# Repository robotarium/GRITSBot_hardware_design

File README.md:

- [Overview](#overview)
- [Getting Started](#getting-started)
- [Hardware Specifications](#hardware-specifications)
- [Hardware Assembly](#hardware-assembly)

# Overview
This repository contains the GRITSBot's circuit board designs, bill of materials, hardware specifications, and 3D design files. This README file is meant to provide more detailed hardware specifications and a brief tutorial outlining how to get started with the hardware. Specifically, it explains how to program both the motor and the main board.

# Getting Started
The newest version of the GRITSBot features two microcontrollers - an Atmega168/328 (8MHz, 16/32 KB flash, 2 KB RAM) on the motor board and the ESP8266 (80/160 MHz, ~80kB DRAM (Data RAM), ~35kB IRAM (Instruction RAM)) on the main board. Both boards can be programmed through the Arduino IDE but require different toolchains (avr-gcc and Xtensa). Both boards have broken out pins to connect the programmer to. The motor board relies on SPI communication for programming, while the main board's ESP8266 chip has a built-in serial bootloader. Therefore the main board requires only a USB-to-TTL converter to program instead of a programmer for the motor board. Note that for programming, the robot has to be disassembled, i.e. the two boards have to be taken apart (the battery does not have to be disconnected, but it's advisable that the robot's power switch is in the OFF position).

## Motor board programming
The GRITSBot's motor board firmware is available [here](https://github.com/robotarium/GRITSBot_firmware). Before programming the motor board, download all required libraries from that link and copy them to the Arduino IDE's 'libraries' folder.

1. Connect the 6-pin ISP single row programming header (shown in the picture) to the female SPI header pins on the motor board (note that for size reasons, the programming connector on the motor board is a two-row 0.127 inch pitch connector and may require an adapter.)
2. Plug the programmer into the USB port on your host machine (ideally running Linux).
3. Programming the Atmega168/328 chip can be done in a variety of ways 
  * Use a tool called arduino-cmake, a CMake-based toolchain customized for the use of avrdude. The initial setup can be tricky but the tool itself is convenient.
  * Add a board definition to the Arduino IDE's boards.txt file that allows direct programming of the motor board through a programming device in the Arduino IDE.
  * If you have compiled your code already and have a .hex file ready to go, you can use avrdude directly as shown below.

An example of uploading a compiled hex file is shown in the line below, which uploads the "blink.hex" file to the flash memory of an Atmega328 chip through the USB port with the help of an STK500v2 programmer. In the call to _avrdude_ you can see the _-C_ parameter to include its configuration file _avrdude.conf_.
```
avrdude -C avrdude.conf -v -v -v -patmega328 -cstk500v2 -Pusb -Uflash:w:./blink.hex:i -Ulock:w:0x0F:m

```

## Main board programming 
Programming the main board is simpler, since it can be done via a serial adapter. However, attention has to be paid to the operating voltage of the main board, which is 3.3V. The ESP8266 chip is NOT 5V-tolerant and both the supply voltage as well as the serial data signals have to be 3.3V. The following steps assume that your Arduino IDE is set up according to [Sparkfun's tutorial](https://learn.sparkfun.com/tutorials/esp8266-thing-hookup-guide/installing-the-esp8266-arduino-addon). It also assumes that you have downloaded all the GRITSBot's firmware libraries into your Arduino/libraries folder. Then the following steps will program the main board. Note that the GRITSBot's main board firmware is available [here](https://github.com/robotarium/GRITSBot_firmware).

1. Set the "Bootmode" switch on the main board to "Flash" (this ensures that the GPIO0 of the ESP8266 is pulled to logic LOW).
2. Press the push botton on the board to reset the board into programming mode in case the board was powered on before.
3. Select *Generic ESP8266 Module* in the board list of the Arduino IDE (Upload speed can be as high as 921000 Baud, depending on your FTDI adapter).
4. Connect the FTDI serial adapter to the main board and plug the other end into a USB port. Make sure the adapter operates at 3.3V (the broken out pins on the main board contain TX, RX, VCC, and GND).
5. Upload code to the board through the Arduino IDE.

# Hardware Specifications
The robot consists of two individual boards that are stacked through a combination of male and female header pins. 

The main board is the central processing board and responsible for the high-level control of the robot, communication, and power supply. As such, it contains the main microcontroller and a WiFi transceiver. The following list summarizes the main components of the main board.

1. The ESP8266 microcontroller that also hosts the WiFi hardware and runs the WiFi stack in software. The ESP8266 chip contains an SPI-controlled EEPROM chip that enables the chip to be wirelessly reprogrammed. The newest version of the GRITSBot contains the ESP8266 12-E with 4 MB (32 MBit) of flash memory, which allows firmware upgrades over-the-air ([see Adafruit](https://www.adafruit.com/products/2491)).
2. MCP73831 LiPo battery charging chip
3. AP2112K-3.3V 3.3V voltage regulator (capable of providing 600 mA of current, which is necessary since the ESP8266 can have peak current consumptions of 300 mA)
4. MCP1640 step-up converter for powering the motors on the motor board (capable of providing 150 mA)
5. INA219 I2C-enabled current and voltage sensor 
6. ATECC108 encryption and authentication chip

The following two images show the top and the bottom layer of the main board PCV

The motor board contains all components related to locomotion including a microcontroller to control the stepper motors. An additional EEPROM chip allows storing calibration parameters and equips each motor board with a unique ID. Additionally, the motor board contains downward-facing infrared sensors for line-following applications as well as introspective sensors to measure the state of the motor board (e.g. currents and temperatures).

1. One Atmega168/328 microcontroller (the motor board firmware requires over 9 KB which excludes the Atmega88 chip)
2. Two LB1836M motor drivers
3. Two miniature stepper motors
4. One 24AA025UIDT-I/OT 2KBIT I2C EEPROM chip providing a unique ID to each motor board.
5. Two QRE1113 downward-facing infrared line sensors 
6. Two STLM20 temperature sensors measuring motor temperatures
7. Two ZXCT1009 current sensors measuring motor currents
6. Reverse polarity circuitry protecting charger input pins
7. Two LEDs for visual output and debugging

The following two images show the top and the bottom layer of the main board PCV

# Hardware Assembly
Assembly of the GRITSBot is fairly simple in the sense that few components have to be added once all the circuit boards have been populated with SMD components (services such as Seeedstudio or Circuithub can manufacture and populate the boards for a reasonable price). Manufacturers can also populate the throughhole components (i.e. the male and female header pins) but so far we have done that manually. The main and motor boards have matching male/female headers that can only be stacked in one way. The __assembly sequence__ contains the following steps. 

## Main board assembly
1. Solder a female Losi Micro Walkera 2-Pin Connector plug to the main board's battery pins (i.e. VBAT and neighboring GND pin)
2. Solder a 4-pin male programming header pin to the top of the main board (i.e. the pins TX, RX, Vcc, GND). Note that the top side of the board is the one with the ESP8266 12-E part.
3. Solder four 2-pin male header pins to all four corners on the bottom of the main board. In the schematic and board files, these pins are labeled JP\_RST, JP\_I2C, JP\_GND, and JP\_VCHRG\_IN.
4. Solder a 3-pin female header pin to the power pins in the center of the bottom of the board (labeled "MOTOR", containing the pins Vcc, Vdd, and GND).

## Motor board assembly
The motor board assembly contains a few more steps since the motors have to be soldered on besides the male and female header pins. In addition, the Qi charging coil and receiver circuitry have to be attached to the board. 

### Prepare and mount the motors and wheels
1. Tap the wheels with an M1.7 thread plug.
2. Screw one wheel onto each motor.
3. Solder both motors onto the motor board (a video showing this procedure will follow soon)

### Solder on the connectors
1. Solder four 2-pin female header pins to all four corners on the top of the motor board. In the schematic and board files, these pins are labeled JP\_RST, JP\_I2C, JP\_GND, and JP\_VCHRG.
2. Solder a 3-pin male header pin to the power pins in the center of the top of the motor board (containing the pins Vcc, Vdd, and GND).

### Prepare the Qi receiver parts
1. Disassemble the Qi receiver pad (see bill of materials specifying which receiver pad to purchase).
2. Desolder the USB connector and the coil from the receiver assembly.

### Attach the Qi receiver parts
1. Glue or tape the Qi receiver coil to the 3D part [Charging Coil Base](https://github.com/robotarium/GRITSBot_hardware_design/blob/master/3d_model/Charging_frame_base.stp).
2. Tape the Qi receiver circuitry to the top of the motor board.
3. Solder a wire to each output pin of the receiver circuitry (those pins should be labeled '+' and '-' or '5V' and 'Gnd').
4. Solder the other end of these wires to the following motor board pins: JP\_CHRG\_L and JP\_CHRG\_R
5. Cut the receiver coil wires to the right length and solder them to the input pins of the receiver circuitry. Those pins may not be labeled on the receiver circuitry, but attach them to the same pins that you desoldered them before.

## Robot assembly
2. Sandwich the battery between the motor and the main board and wrap the battery cable around the robot.
3. Stack the motor and the main board keeping the battery in place.
5. Connect battery to the main board.

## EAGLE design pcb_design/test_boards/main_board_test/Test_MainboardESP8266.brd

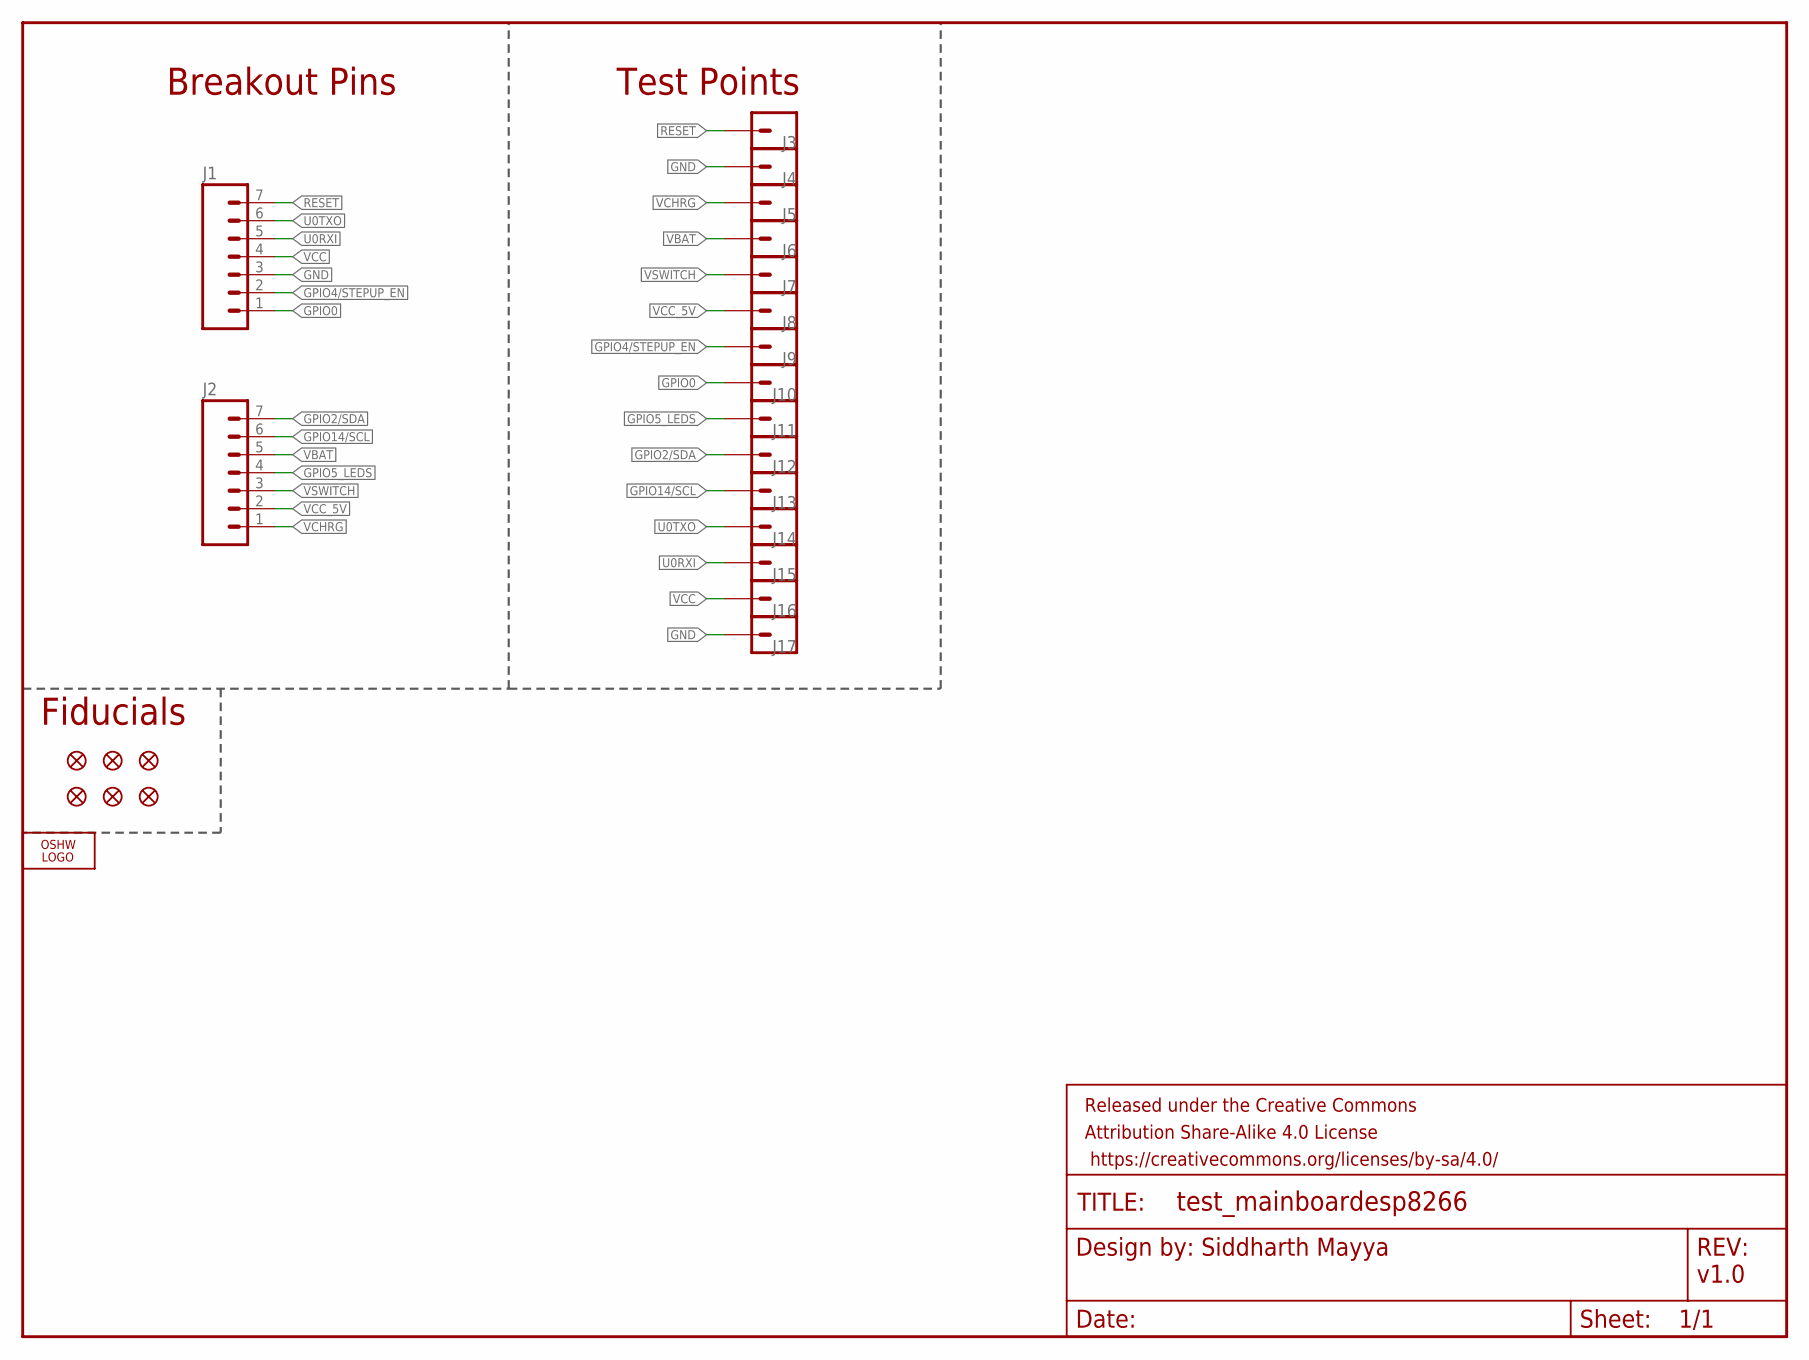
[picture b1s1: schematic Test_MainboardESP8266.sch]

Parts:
FD1, FD2, FD3, FD4, FD5, FD6: FIDUCIAL1X2; FIDUCIAL-1X2
FRAME1: FRAME-LETTER; CREATIVE_COMMONS
J1, J2: M07; 1X07
J3, J4, J5, J6, J7, J8, J9, J10, J11, J12, J13, J14, J15, J16, J17: M01PTH; 1X01
LOGO1: OSHW_LOGO_FILLX0100-NT; OSHW_FILLX100_NOTEXT

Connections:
GND: J1.3, J4.1, J17.1
GPIO0: J1.1, J10.1
GPIO2/SDA: J2.7, J12.1
GPIO4/STEPUP_EN: J1.2, J9.1
GPIO5_LEDS: J2.4, J11.1
GPIO14/SCL: J2.6, J13.1
RESET: J1.7, J3.1
U0RXI: J1.5, J15.1
U0TXO: J1.6, J14.1
VBAT: J2.5, J6.1
VCC: J1.4, J16.1
VCC_5V: J2.2, J8.1
VCHRG: J2.1, J5.1
VSWITCH: J2.3, J7.1

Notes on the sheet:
v1.0
Test Points
Breakout Pins
Fiducials

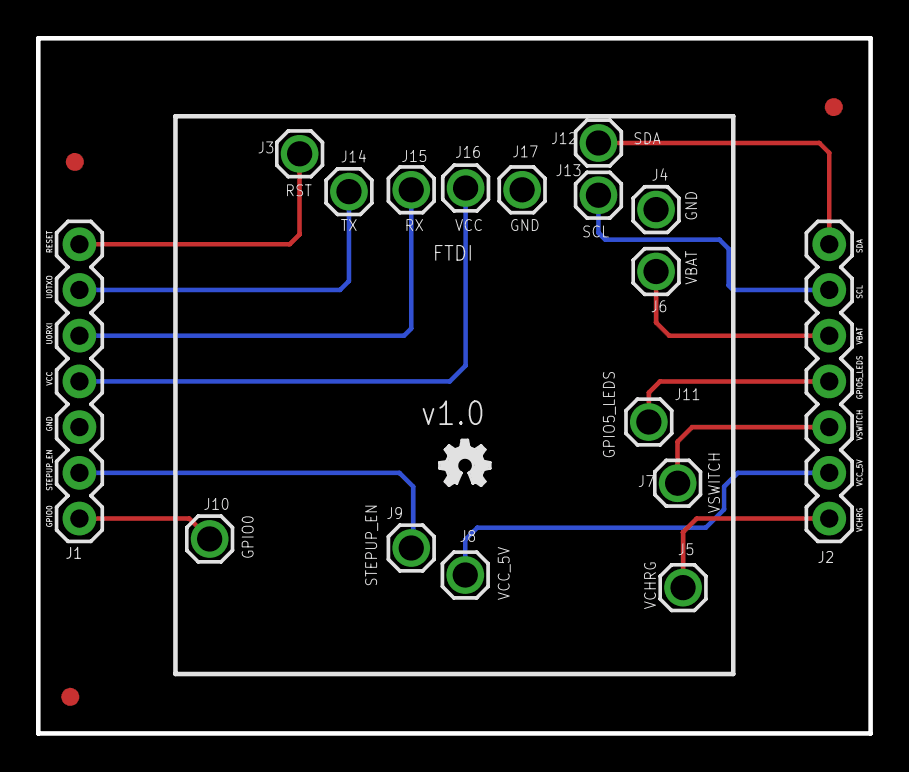
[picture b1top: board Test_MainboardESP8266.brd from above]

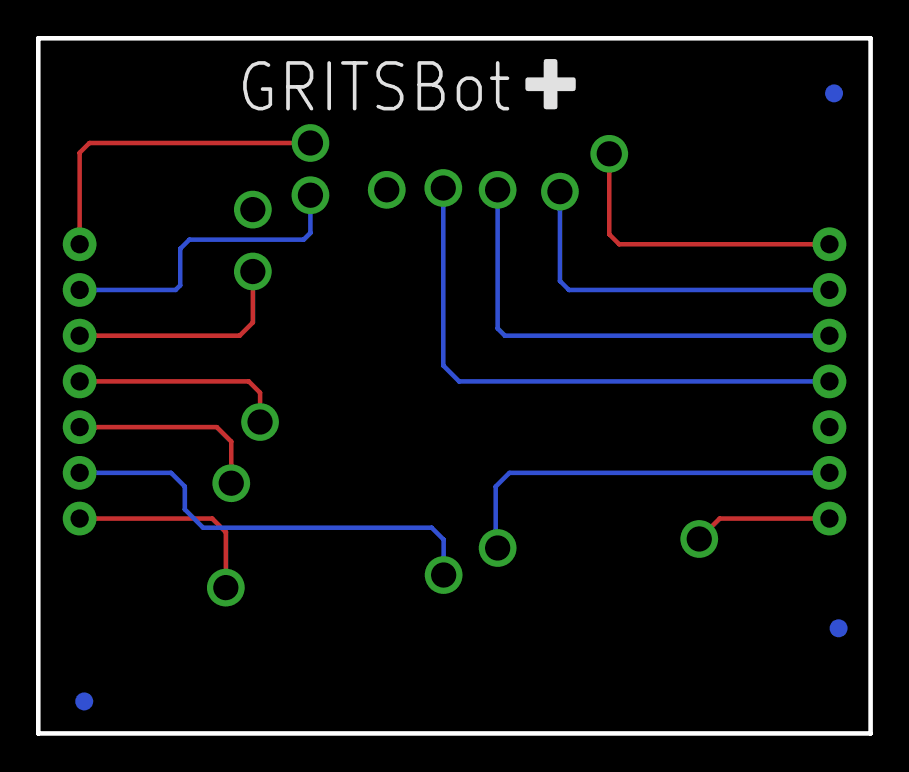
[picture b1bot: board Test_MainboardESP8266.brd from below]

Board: 2 copper layers, 46.2 x 38.6 mm, 25 parts (3 on the bottom side), 14 nets.

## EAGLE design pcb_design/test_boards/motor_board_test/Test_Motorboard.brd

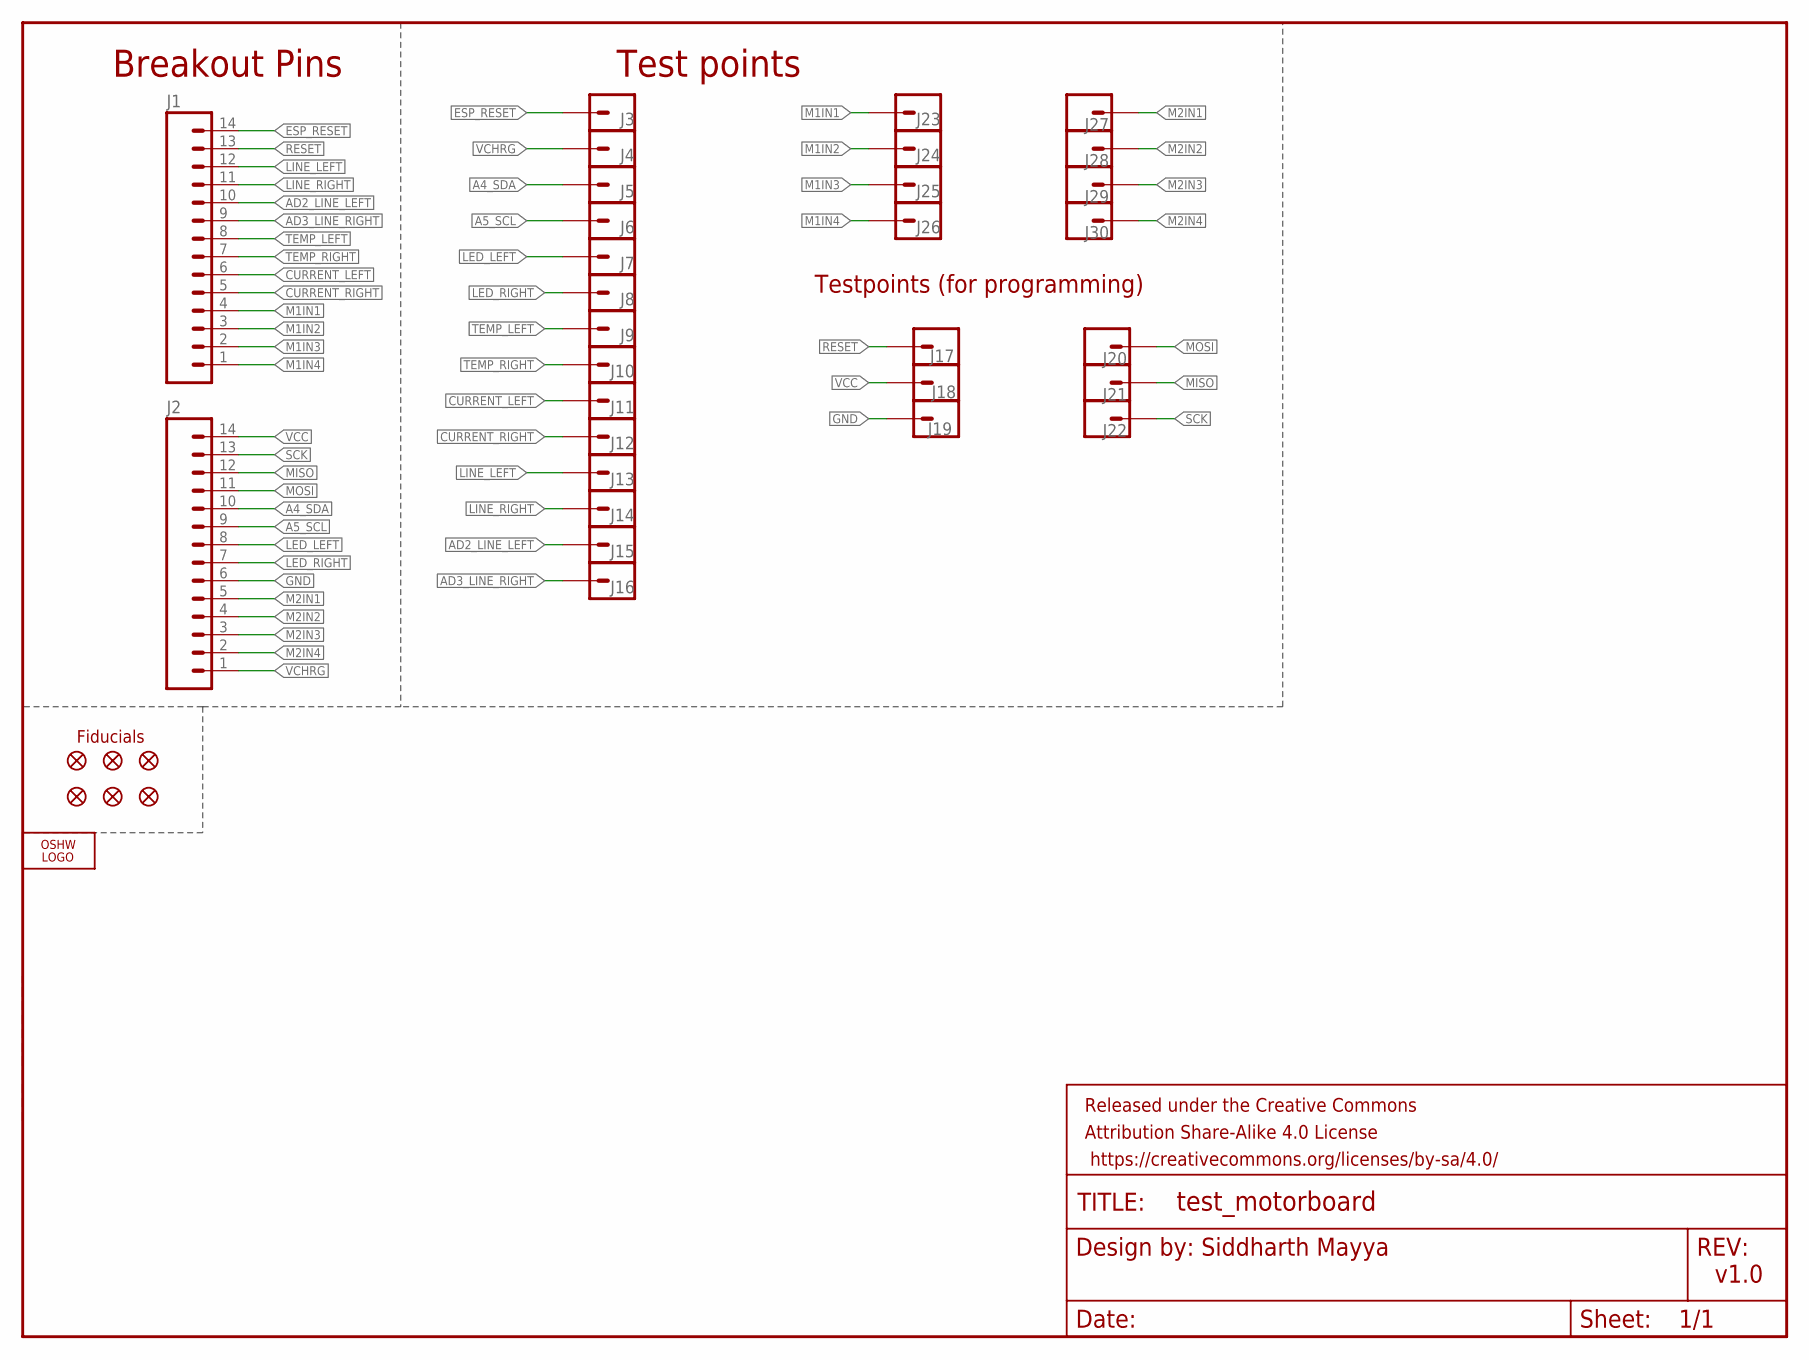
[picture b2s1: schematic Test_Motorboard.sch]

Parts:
FD1, FD2, FD3, FD4, FD5, FD6: FIDUCIAL1X2; FIDUCIAL-1X2
FRAME1: FRAME-LETTER; CREATIVE_COMMONS
J1, J2: M14; 1X14
J3, J4, J5, J6, J7, J8, J9, J10, J11, J12, J13, J14, J15, J16, J17, J18, J19, J20, J21, J22, J23, J24, J25, J26, J27, J28, J29, J30: M01PTH; 1X01
LOGO1: OSHW_LOGO_FILLX0100-NT; OSHW_FILLX100_NOTEXT

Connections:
A4_SDA: J2.10, J5.1
A5_SCL: J2.9, J6.1
AD2_LINE_LEFT: J1.10, J15.1
AD3_LINE_RIGHT: J1.9, J16.1
CURRENT_LEFT: J1.6, J11.1
CURRENT_RIGHT: J1.5, J12.1
ESP_RESET: J1.14, J3.1
GND: J2.6, J19.1
LED_LEFT: J2.8, J7.1
LED_RIGHT: J2.7, J8.1
LINE_LEFT: J1.12, J13.1
LINE_RIGHT: J1.11, J14.1
M1IN1: J1.4, J23.1
M1IN2: J1.3, J24.1
M1IN3: J1.2, J25.1
M1IN4: J1.1, J26.1
M2IN1: J2.5, J27.1
M2IN2: J2.4, J28.1
M2IN3: J2.3, J29.1
M2IN4: J2.2, J30.1
MISO: J2.12, J21.1
MOSI: J2.11, J20.1
RESET: J1.13, J17.1
SCK: J2.13, J22.1
TEMP_LEFT: J1.8, J9.1
TEMP_RIGHT: J1.7, J10.1
VCC: J2.14, J18.1
VCHRG: J2.1, J4.1

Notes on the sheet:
Breakout Pins
Testpoints (for programming)
Test points
Fiducials
v1.0

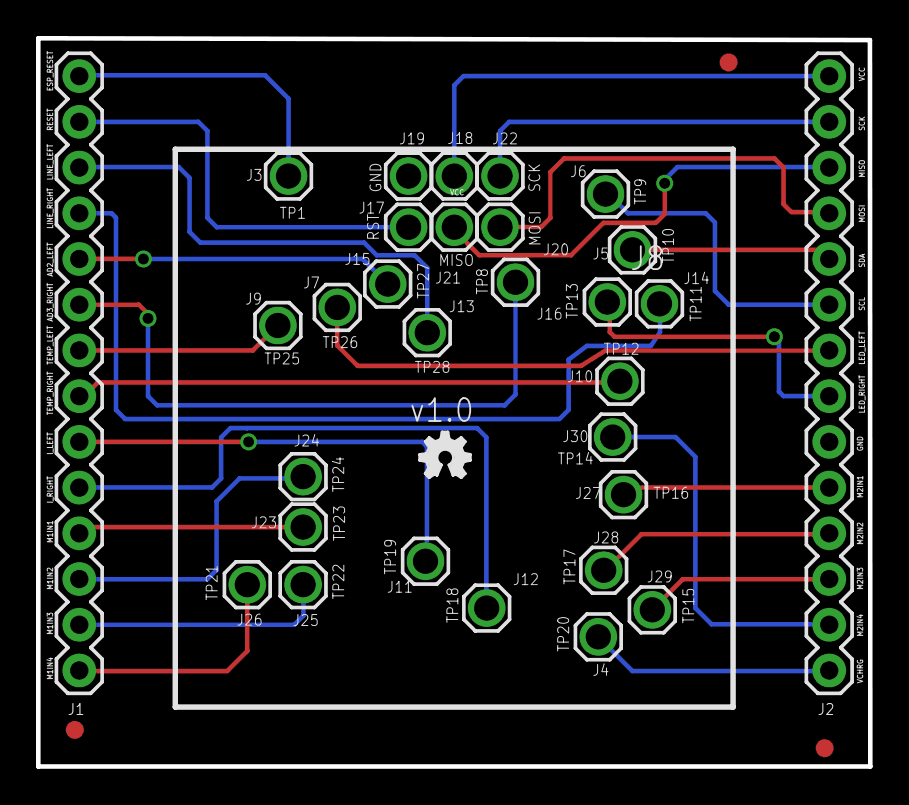
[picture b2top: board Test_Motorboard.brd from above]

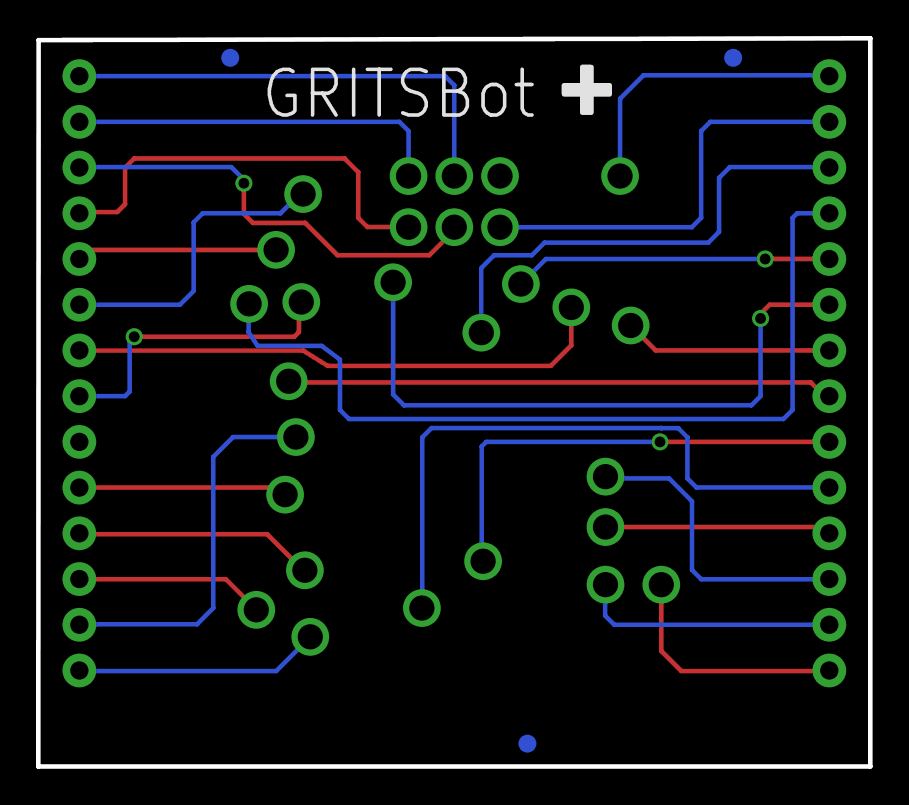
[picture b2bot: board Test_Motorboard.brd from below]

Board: 2 copper layers, 46.2 x 40.5 mm, 39 parts (3 on the bottom side), 28 nets.

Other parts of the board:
FRAME3: FRAME-LETTER; CREATIVE_COMMONS

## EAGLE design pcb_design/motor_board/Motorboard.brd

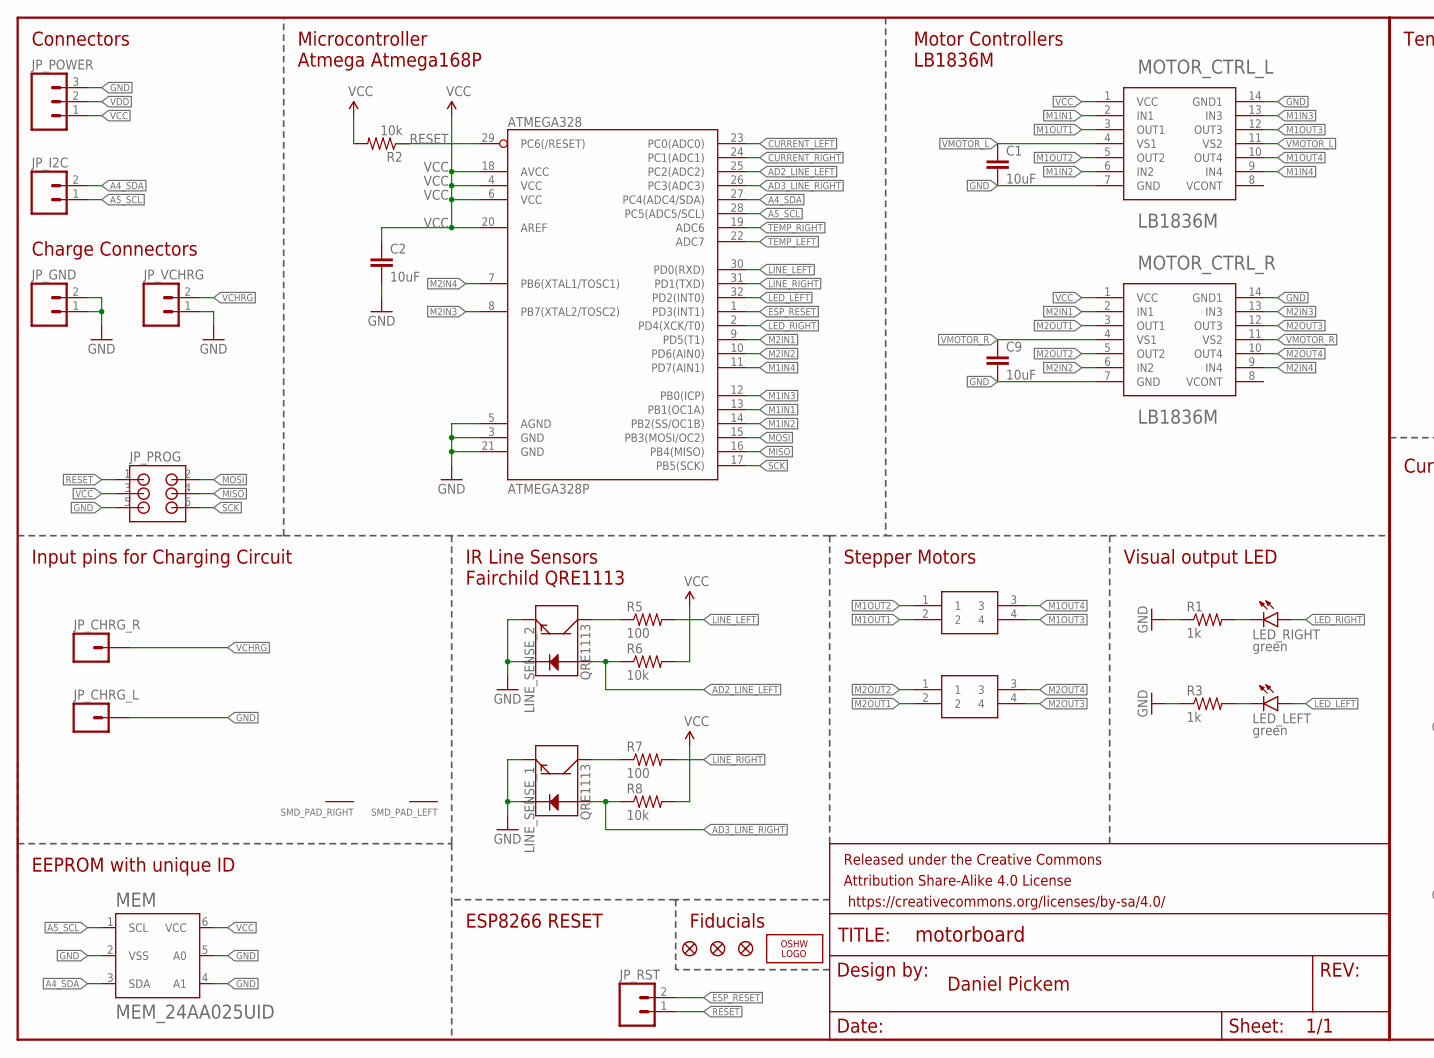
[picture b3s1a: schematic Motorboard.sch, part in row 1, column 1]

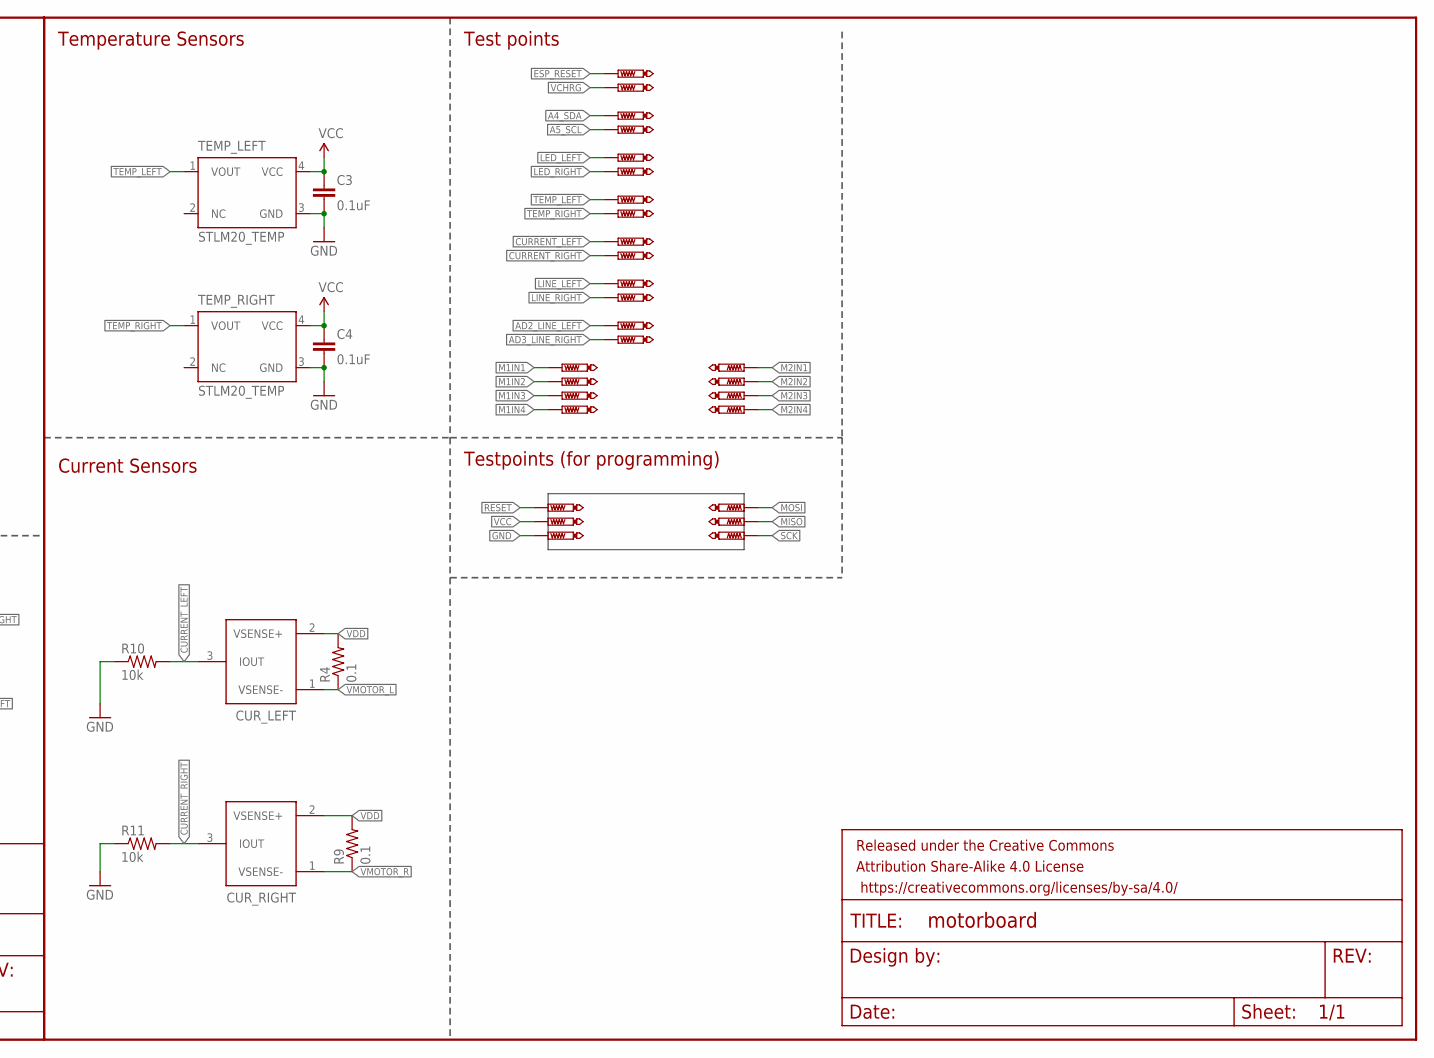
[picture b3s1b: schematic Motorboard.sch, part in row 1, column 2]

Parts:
ATMEGA328P: ATMEGA328; TQFP32-08
C1, C2, C9: 10uF; 0805
C3, C4: 0.1uF; 0603-CAP
CUR_LEFT: ZXCT1009_CURRENT; SOT23-3
CUR_RIGHT: ZXCT1009_CURRENT; SOT23-3
FRAME1, FRAME2: FRAME-LETTER; CREATIVE_COMMONS
JP3, JP4, JP5: FIDUCIAL1X2.5; FIDUCIAL-1X2.5
JP_CHRG_L: M01NOSILK-KIT; 1X01NS-KIT
JP_CHRG_R: M01NOSILK-KIT; 1X01NS-KIT
JP_GND: M021X02_NO_SILK; 1X02_NO_SILK
JP_I2C: M02PTH; 1X02
JP_POWER: supply; 1X03
JP_PROG: 3X2_SMD_HEADER
JP_RST: M021X02_NO_SILK; 1X02_NO_SILK
JP_VCHRG: M021X02_NO_SILK; 1X02_NO_SILK
LED_LEFT: green; LED-0603
LED_RIGHT: green; LED-0603
LINE_SENSE_1, LINE_SENSE_2: QRE1113
LOGO1: OSHW_LOGO_FILLX0100-NT; OSHW_FILLX100_NOTEXT
M1, M2: STEPPER_MOTOR_SMD
MEM: MEM_24AA025UID; SOT23-6-MCP1640
MOTOR_CTRL_L: LB1836M; LSOP-14
MOTOR_CTRL_R: LB1836M; LSOP-14
R1, R3: 1k; 0603
R2, R6, R8, R10, R11: 10k; 0603
R4, R9: 0.1; 1206
R5, R7: 100; 0603
SMD_PAD_LEFT: PIN_SMD2.5X1.0; PIN_SMD_2.5X1.0
SMD_PAD_RIGHT: PIN_SMD2.5X1.0; PIN_SMD_2.5X1.0
TEMP_LEFT: STLM20_TEMP; UDFN4
TEMP_RIGHT: STLM20_TEMP; UDFN4
TP1, TP2, TP3, TP4, TP5, TP6, TP7, TP8, TP9, TP10, TP11, TP12, TP13, TP14, TP15, TP16, TP17, TP18, TP19, TP20, TP21, TP22, TP23, TP24, TP25, TP26, TP27, TP28: PTR1B1,27; B1,27

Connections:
A4_SDA: ATMEGA328P.27 (PC4(ADC4/SDA)), JP_I2C.2, MEM.3 (SDA), TP10.TP
A5_SCL: ATMEGA328P.28 (PC5(ADC5/SCL)), JP_I2C.1, MEM.1 (SCL), TP9.TP
AD2_LINE_LEFT: ATMEGA328P.25 (PC2(ADC2)), LINE_SENSE_2.1 (A), R6.1, TP27.TP
AD3_LINE_RIGHT: ATMEGA328P.26 (PC3(ADC3)), LINE_SENSE_1.1 (A), R8.1, TP8.TP
CURRENT_LEFT: ATMEGA328P.23 (PC0(ADC0)), CUR_LEFT.3 (IOUT), R10.2, TP19.TP
CURRENT_RIGHT: ATMEGA328P.24 (PC1(ADC1)), CUR_RIGHT.3 (IOUT), R11.2, TP18.TP
ESP_RESET: ATMEGA328P.1 (PD3(INT1)), JP_RST.2, TP1.TP
GND: ATMEGA328P.3 (GND), ATMEGA328P.5 (AGND), ATMEGA328P.21 (GND), C1.2, C2.2, C3.2, C4.1, C9.2, JP_CHRG_L.1, JP_GND.1, JP_GND.2, JP_POWER.3, JP_PROG.5, JP_VCHRG.1, LINE_SENSE_1.2 (K), LINE_SENSE_1.4 (E), LINE_SENSE_2.2 (K), LINE_SENSE_2.4 (E), MEM.2 (VSS), MEM.4 (A1), MEM.5 (A0), MOTOR_CTRL_L.7 (GND), MOTOR_CTRL_L.14 (GND1), MOTOR_CTRL_R.7 (GND), MOTOR_CTRL_R.14 (GND1), R1.1, R3.1, R10.1, R11.1, TEMP_LEFT.3 (GND), TEMP_RIGHT.3 (GND), TP2.TP
LED_LEFT: ATMEGA328P.32 (PD2(INT0)), LED_LEFT.A, TP26.TP
LED_RIGHT: ATMEGA328P.2 (PD4(XCK/T0)), LED_RIGHT.A, TP13.TP
LINE_LEFT: ATMEGA328P.30 (PD0(RXD)), R5.2, TP28.TP
LINE_RIGHT: ATMEGA328P.31 (PD1(TXD)), R7.2, TP11.TP
M1IN1: ATMEGA328P.13 (PB1(OC1A)), MOTOR_CTRL_L.2 (IN1), TP23.TP
M1IN2: ATMEGA328P.14 (PB2(SS/OC1B)), MOTOR_CTRL_L.6 (IN2), TP24.TP
M1IN3: ATMEGA328P.12 (PB0(ICP)), MOTOR_CTRL_L.13 (IN3), TP22.TP
M1IN4: ATMEGA328P.11 (PD7(AIN1)), MOTOR_CTRL_L.9 (IN4), TP21.TP
M1OUT1: M1.2, MOTOR_CTRL_L.3 (OUT1)
M1OUT2: M1.1, MOTOR_CTRL_L.5 (OUT2)
M1OUT3: M1.4, MOTOR_CTRL_L.12 (OUT3)
M1OUT4: M1.3, MOTOR_CTRL_L.10 (OUT4)
M2IN1: ATMEGA328P.9 (PD5(T1)), MOTOR_CTRL_R.2 (IN1), TP16.TP
M2IN2: ATMEGA328P.10 (PD6(AIN0)), MOTOR_CTRL_R.6 (IN2), TP17.TP
M2IN3: ATMEGA328P.8 (PB7(XTAL2/TOSC2)), MOTOR_CTRL_R.13 (IN3), TP15.TP
M2IN4: ATMEGA328P.7 (PB6(XTAL1/TOSC1)), MOTOR_CTRL_R.9 (IN4), TP14.TP
M2OUT1: M2.2, MOTOR_CTRL_R.3 (OUT1)
M2OUT2: M2.1, MOTOR_CTRL_R.5 (OUT2)
M2OUT3: M2.4, MOTOR_CTRL_R.12 (OUT3)
M2OUT4: M2.3, MOTOR_CTRL_R.10 (OUT4)
MISO: ATMEGA328P.16 (PB4(MISO)), JP_PROG.4, TP6.TP
MOSI: ATMEGA328P.15 (PB3(MOSI/OC2)), JP_PROG.2, TP7.TP
unnamed: LED_LEFT.C, R3.2
unnamed: LINE_SENSE_2.3 (C), R5.1
unnamed: LINE_SENSE_1.3 (C), R7.1
unnamed: LED_RIGHT.C, R1.2
RESET: ATMEGA328P.29 (PC6(/RESET)), JP_PROG.1, JP_RST.1, R2.1, TP5.TP
SCK: ATMEGA328P.17 (PB5(SCK)), JP_PROG.6, TP4.TP
TEMP_LEFT: ATMEGA328P.22 (ADC7), TEMP_LEFT.1 (VOUT), TP25.TP
TEMP_RIGHT: ATMEGA328P.19 (ADC6), TEMP_RIGHT.1 (VOUT), TP12.TP
VCC: ATMEGA328P.4 (VCC), ATMEGA328P.6 (VCC), ATMEGA328P.18 (AVCC), ATMEGA328P.20 (AREF), C2.1, C3.1, C4.2, JP_POWER.1, JP_PROG.3, MEM.6 (VCC), MOTOR_CTRL_L.1 (VCC), MOTOR_CTRL_R.1 (VCC), R2.2, R6.2, R8.2, TEMP_LEFT.4 (VCC), TEMP_RIGHT.4 (VCC), TP3.TP
VCHRG: JP_CHRG_R.1, JP_VCHRG.2, TP20.TP
VDD: CUR_LEFT.2 (VSENSE+), CUR_RIGHT.2 (VSENSE+), JP_POWER.2, R4.2, R9.2
VMOTOR_L: C1.1, CUR_LEFT.1 (VSENSE-), MOTOR_CTRL_L.4 (VS1), MOTOR_CTRL_L.11 (VS2), R4.1
VMOTOR_R: C9.1, CUR_RIGHT.1 (VSENSE-), MOTOR_CTRL_R.4 (VS1), MOTOR_CTRL_R.11 (VS2), R9.1

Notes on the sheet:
Connectors
Microcontroller Atmega Atmega168P
Visual output LED
Motor Controllers LB1836M
Stepper Motors
IR Line Sensors Fairchild QRE1113
ESP8266 RESET
Fiducials
Daniel Pickem
Charge Connectors
Input pins for Charging Circuit
Temperature Sensors
Current Sensors
EEPROM with unique ID
Testpoints (for programming)
Test points

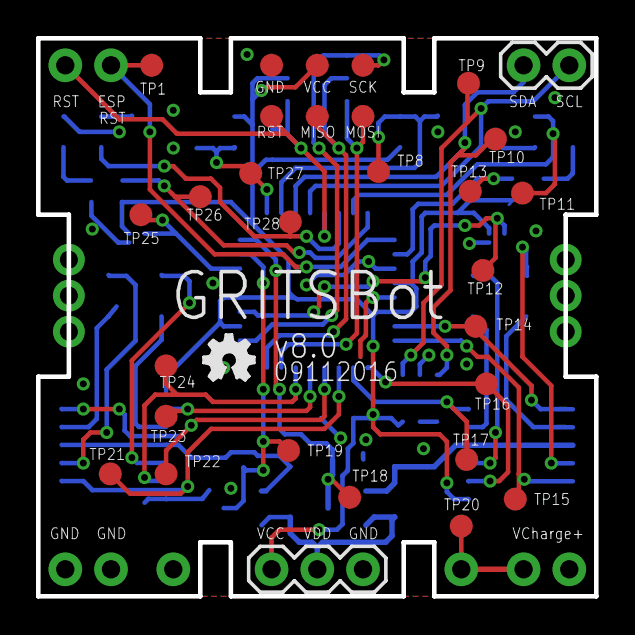
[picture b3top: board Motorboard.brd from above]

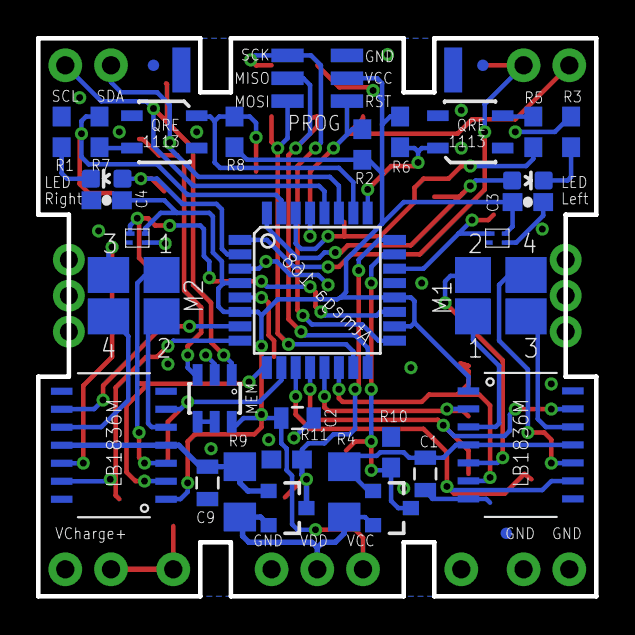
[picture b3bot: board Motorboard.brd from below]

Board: 2 copper layers, 31.0 x 31.0 mm, 75 parts (36 on the bottom side), 43 nets.

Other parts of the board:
FRAME3: FRAME-LETTER; CREATIVE_COMMONS

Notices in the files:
pcb_design/main_board/MainboardESP8266.brd:
Released under the Creative Commons Attribution Share-Alike 4.0 License
https://creativecommons.org/licenses/by-sa/4.0
parts and their libraries:
SparkFun-Resistors: Licensing: Creative Commons ShareAlike 4.0 International - https://creativecommons.org/licenses/by-sa/4.0
GRITSBot: Released under the Creative Commons
